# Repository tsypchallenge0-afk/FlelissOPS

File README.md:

# AviFarm · FlelissOPS — Smart Poultry Management System

AviFarm (dashboard brand: **FlelissOPS**) is an IoT + AI platform for commercial poultry houses. ESP32 sensor nodes stream temperature, humidity and ammonia over MQTT; a FastAPI backend stores them in MongoDB, forecasts and detects anomalies, and runs a closed control loop over fans, heaters, lighting and feeders. A multi-tenant React dashboard serves each client on its own sub-domain, with a separate super-admin console.

---

## Architecture

```text
 ESP32 + DHT22 + MQ-135 ──MQTT──►  Mosquitto  ──►┐
 Simulators (HTTP) ─────────────────────────────►├── FastAPI backend (:9000)        React dashboard (:5173)
                                                 │   telemetry · alerts · AI ──WS──► <tenant>.lvh.me
                                                 │   control loop · flocks           super.lvh.me (super admin)
 Actuator ESP32 (fans/heater/…) ◄──MQTT commands─┘          │
                                                        MongoDB
```

| Layer | Tech | Code |
|---|---|---|
| Hardware | ESP32, DHT22, MQ-135, actuator node | [`hardware/`](hardware/) |
| Messaging | MQTT (Mosquitto), WebSockets | [`mosquitto/`](mosquitto/), [`back_end/app/core/mqtt.py`](back_end/app/core/mqtt.py) |
| Backend | FastAPI, PyMongo, APScheduler | [`back_end/app/`](back_end/app/) |
| AI | Prophet forecasting, Isolation-Forest anomalies, rule/AI control loop | [`back_end/app/ai/`](back_end/app/ai/) |
| Frontend | React 19, Vite, Recharts, dnd-kit | [`poultry-dashboard/`](poultry-dashboard/) |

## Features

- **Command Center & House Control** — live gauges (temperature, humidity, ammonia, heat-stress index THI), alerts, manual/AI control of fans, heater, lighting and feeder.
- **Spatial view** — cut-away 3-D house with every sensor at its installed position, an interpolated floor heat-map (temperature / humidity / NH₃), live equipment state, and drag-to-reposition sensors.
- **Flock management** — placements, weigh-ins, feed, mortality; KPIs: mortality %, FCR, weight vs breed standard (Ross 308 / Cobb 500), EPEF; age-based setpoint curves.
- **Health score** — weighted from temperature vs age target, ammonia and survival.
- **AI** — Prophet forecasts, Isolation-Forest anomaly detection, autonomous control loop with a decision log (AI automation rate is measured, not assumed).
- **Analytics & reports** — farm comparison, efficiency, alert patterns, PDF reports and scheduled e-mail reports.
- **Multi-tenancy** — each client on `<subdomain>.lvh.me`, plan quotas, invitations, super-admin console.

---

## Quick start (local)

**Prerequisites:** Docker Desktop, Python 3.11+ (verified on 3.14), Node.js 18+ (verified on 24).

### 1. Infrastructure (MongoDB, Mongo Express, Mosquitto)
```bash
docker compose up -d
```
MongoDB `:27017` (user `admin` / `password`), Mongo Express http://localhost:8081, MQTT `:1883`.

### 2. Backend
```bash
cd back_end
python -m venv .venv
.venv\Scripts\activate            # macOS/Linux: source .venv/bin/activate
pip install -r requirements.txt   # includes PyTorch — large download
copy .env.example .env            # macOS/Linux: cp .env.example .env
uvicorn app.main:app --reload --port 9000
```
API docs: http://localhost:9000/docs. The port must be **9000** — the frontend proxies `/api` there.

### 3. Seed data
```bash
cd back_end
python -m scripts.seed_dev --demo
```
Creates the `default` tenant, alert rules, a **super admin** (`superadmin`) and a **tenant admin** (`admin@test.com`) — the generated passwords are printed once (or set `SEED_SUPERADMIN_PASSWORD` / `SEED_ADMIN_PASSWORD` first). `--demo` adds the simulator's farms/houses/sensors and an active flock with realistic history in every house. Safe to re-run; existing users are left untouched (`--reset-passwords` to change that).

### 4. Frontend
```bash
cd poultry-dashboard
copy .env.example .env
npm install
npm run dev
```

### 5. Open it
| URL | What |
|---|---|
| http://default.lvh.me:5173 | Tenant dashboard (`admin@test.com`) |
| http://super.lvh.me:5173 | Super-admin console (`superadmin`) |
| http://localhost:9000/docs | API |

> The tenant comes from the sub-domain, so use `*.lvh.me`, not `localhost`. `lvh.me` resolves to 127.0.0.1 through **public DNS** — for an offline demo add these lines to `C:\Windows\System32\drivers\etc\hosts` (or `/etc/hosts`):
> ```
> 127.0.0.1  lvh.me default.lvh.me super.lvh.me
> ```
> plus one line per extra tenant sub-domain. Fonts are bundled, so the UI looks identical offline.

### 6. Live data without hardware
```bash
cd back_end
python -m simulator.runner --live      # one reading per simulated sensor per minute
python -m simulator.runner --backfill  # 21 days of history (for AI training/analytics)
```

### 7. Heat-stress demo (about 1 minute)
Open a house → **▶ HEAT-STRESS DEMO** (supervisor/admin). The backend replays a heat wave on that house's real sensors; everything else is the production pipeline: readings are stored and broadcast, alert rules fire (one alert per condition, no flood), the AI decision function runs on the stored data and its commands go out exactly like the 30-second control loop (actuator state, audit log, WebSocket, MQTT to the hardware). The panel shows the phases, peak temperature, alerts and the **measured breach → AI-command latency**. If the fans are in MANUAL mode the AI is, correctly, not allowed to override them. Demo readings are tagged `source: "demo_scenario"`. API: `POST /houses/{id}/demo/heat-stress`, `GET /houses/{id}/demo/status`.

---

## Tests

```bash
cd back_end
pip install -r requirements-dev.txt
set MONGO_URL=mongodb://admin:password@127.0.0.1:27017/?authSource=admin   # export on macOS/Linux
python -m pytest
```
The suite ([`back_end/tests/`](back_end/tests/)) runs against a throw-away `poultry_test` database (created and dropped automatically — it refuses to run against any database not ending in `_test`) and covers auth & tenant isolation, farm → house → device → telemetry → alert flow, flock KPIs, controls, maintenance and super-admin access.

Frontend: `cd poultry-dashboard && npm run lint && npm run build`.

---

## Hardware (MQTT)

**Sensor node** — [`hardware/sensor_node_esp32/`](hardware/sensor_node_esp32/)
- DHT22 (temperature/humidity) on GPIO 4, MQ-135 (ammonia) on GPIO 34.
- Libraries: `DHT sensor library`, `PubSubClient`, `ArduinoJson`.
- Set `ssid`, `password` and `mqtt_server` (the PC's LAN IP) in the `.ino`.

Publish JSON to topic `telemetry/send`:
```json
{ "device_id": "69aac9a67dee4c1c93b052ee", "temperature": 28.5, "humidity": 65.0, "ammonia": 12.4 }
```
The backend looks the device up, tags the reading with its tenant and house, marks it online and evaluates alert rules. Unknown device IDs are listed as discovered devices and can be adopted in the device registration drawer. A sensor that has not reported for 15 minutes is shown offline.

**Actuator node** — [`hardware/actuator_node_esp32/`](hardware/actuator_node_esp32/) receives control commands over MQTT.

**PCBs (revision 2.0, KiCad 9)** — schematics, board layouts, 3D renders and ready-to-order Gerbers for both nodes are in [`hardware/pcb/`](hardware/pcb/); see [`hardware/README.md`](hardware/README.md) for the parts list and notes.

---

## Troubleshooting

| Symptom | Fix |
|---|---|
| Backend: `Authentication failed` from MongoDB on Windows | A local **MongoDB Windows service** also listens on `127.0.0.1:27017` and wins over Docker. Use `MONGO_URL=mongodb://admin:password@[::1]:27017/?authSource=admin` (the default in `.env.example`), or stop the service (`net stop MongoDB`). |
| `Tenant "default" not found` | Open the app on `default.lvh.me`, and run the seed script. |
| Page does not load when offline | Add the hosts-file entries above. |
| `pip install` fails on numpy/pandas | Use the pinned `requirements.txt` (old pins do not support Python 3.13+). |
| Warning `JWT_SECRET is not set` | Set `JWT_SECRET` in `back_end/.env`. |

---

## Project structure

```text
back_end/
  app/            FastAPI routers (auth, farms, houses, devices, telemetry, alerts, flock, ai, control, analytics, reports, tenants)
  simulator/      physics-based sensor simulator
  scripts/        seed_dev.py and maintenance scripts
  tests/          pytest API suite
poultry-dashboard/
  src/pages       Command Center, House Control, Flock, Analytics, Devices, Alerts, Maintenance, Admin, super-admin
  src/components  gauges, spatial FloorPlanView, health dashboard, curve editor …
  src/lib         API client, tenant helpers, shared constants
hardware/         ESP32 firmware (sensor & actuator nodes)
mosquitto/        broker config
```

## License
Proprietary. All rights reserved.

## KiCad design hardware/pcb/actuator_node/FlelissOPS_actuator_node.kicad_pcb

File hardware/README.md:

# Hardware

Two ESP32-WROOM-32 nodes: a **sensor node** that measures the house climate and an **actuator node** that switches equipment. Both talk to the backend over MQTT (topic `telemetry/send` for readings, `commands/{house_id}/{device}` for control).

```
hardware/
├── sensor_node_esp32/      Arduino firmware — sensor node
├── actuator_node_esp32/    Arduino firmware — actuator node
├── i2c_scanner/            utility sketch to find I²C addresses (OLED)
└── pcb/                    PCB design files, revision 2.0 (KiCad 9)
    ├── sensor_node/
    └── actuator_node/
```

Each board folder under `pcb/` contains:

| Path | What it is |
|---|---|
| `*.kicad_pro`, `*.kicad_sch`, `*.kicad_pcb` | KiCad 9 project, schematic and board layout (open the `.kicad_pro`) |
| `exports/*_schematic.pdf` | Schematic, readable without KiCad |
| `exports/*_pcb_layout.pdf` | Copper, silkscreen and outline layers |
| `exports/*_3d_top.png`, `*_3d_bottom.png` | 3D renders of the assembled board |
| `gerbers/` | Gerber and drill files (RS-274X / Excellon) |
| `*_gerbers_*.zip` | The same Gerbers zipped, ready to upload to a PCB fab |

## Sensor node — 100 × 60 mm

| Ref | Part | Role |
|---|---|---|
| U1 | ESP32-WROOM-32 (DevKit header) | Wi-Fi + MQTT |
| U2 | DHT22 | Temperature / humidity, GPIO 4, 10 kΩ pull-up (R1) |
| J2 | MQ-135 module | Air quality / ammonia, analog on GPIO 34 |
| J1 | SSD1306 OLED (I²C) | Local display |
| J3, C1 | Power input + bulk capacitor | |

## Actuator node — 140 × 100 mm

Mains-powered: it draws its own 5 V from the AC line and switches a fan.

| Ref | Part | Role |
|---|---|---|
| U1 | ESP32-WROOM-32 (DevKit header) | Wi-Fi + MQTT |
| PS1 | HLK-PM01 | 230 V AC → 5 V DC |
| U2 | AMS1117-3.3 | 3.3 V regulator |
| K2 | Omron G5LE-1 relay | Switches the fan (J2 *FAN OUTPUT*) |
| Q2, R1, D1 | NPN driver, 10 kΩ base resistor, 1N4007 flyback diode | Relay coil drive |
| F1 | Fuse | On the AC input (J1 *AC INPUT*) |
| WIFI1, MQTT1, ALARM1 + R2–R4 | Status LEDs, 220 Ω | Wi-Fi, broker and alarm state |
| — | SSD1306 OLED (I²C) | Local display |

> **Mains voltage.** The actuator board carries 230 V AC on J1, PS1, F1, K2 and J2. Keep the high-voltage area enclosed and never work on the board while it is plugged in.

## Firmware and PCB revisions

The firmware in `actuator_node_esp32/` was written on the breadboard prototype and drives four outputs (fan PWM on GPIO 18, heater, feeder and lighting relays on GPIO 19, 5 and 23). PCB revision 2.0 carries **one** relay channel (the fan) plus status LEDs and an OLED. Check the pin mapping in the sketch against `exports/actuator_node_schematic.pdf` before flashing the firmware onto the v2.0 board.

## Before flashing

Both sketches ship with placeholders. Set them first:

```cpp
const char* ssid        = "YOUR_WIFI_SSID";
const char* password    = "YOUR_WIFI_PASSWORD";
const char* mqtt_server = "192.168.1.100";   // LAN IP of the PC running Mosquitto
```

Libraries: `PubSubClient`, `ArduinoJson`, `DHT sensor library` (sensor node), `Adafruit SSD1306` + `Adafruit GFX` (OLED).

## Ordering the boards

Upload the `*_gerbers_*.zip` of a board to any PCB fab (2 layers, 1.6 mm FR-4). To regenerate the exports after editing the design:

```bash
kicad-cli sch export pdf -o exports/<board>_schematic.pdf <project>.kicad_sch
kicad-cli pcb render --side top -o exports/<board>_3d_top.png <project>.kicad_pcb
```

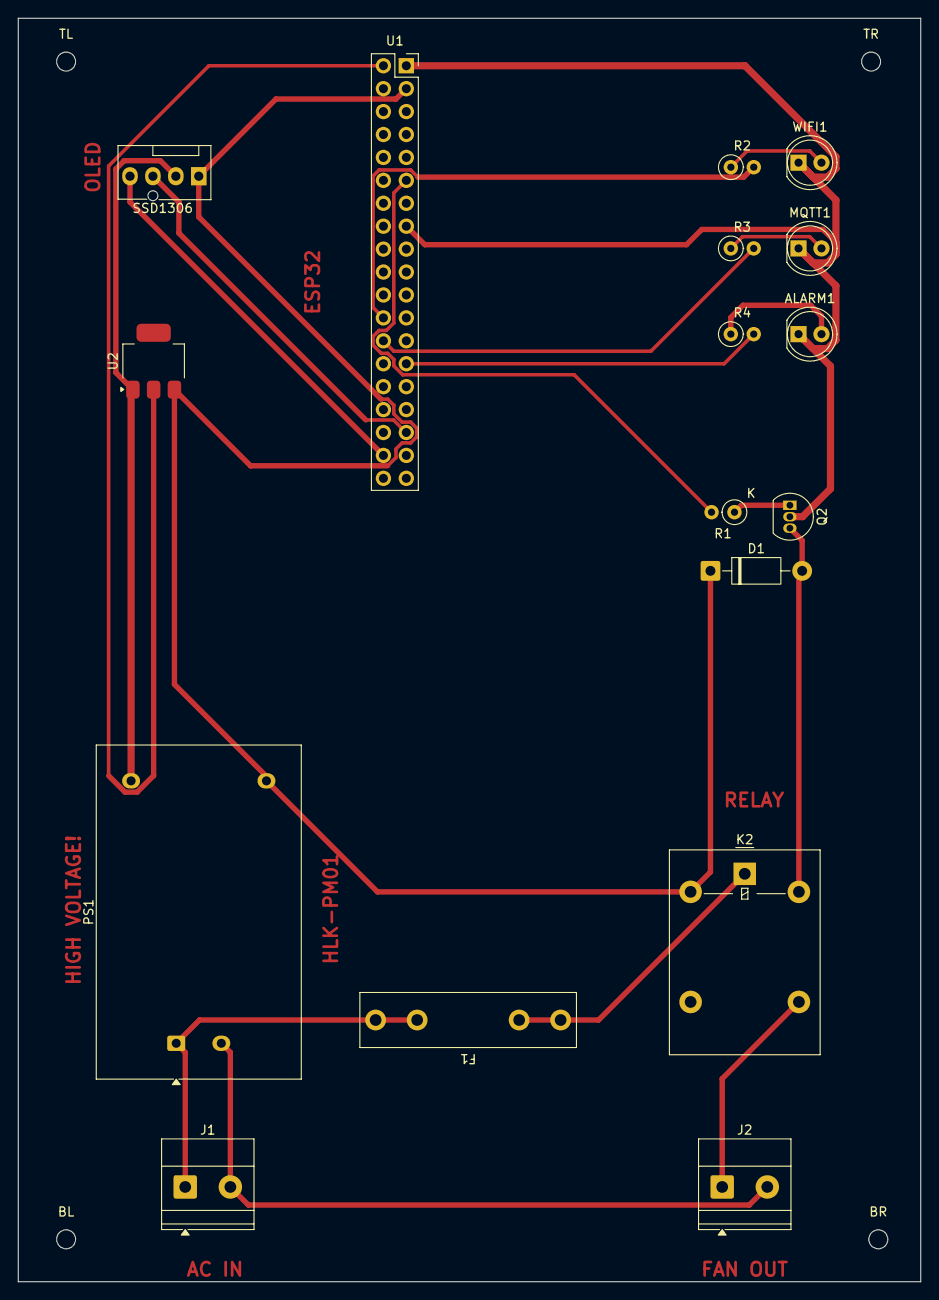
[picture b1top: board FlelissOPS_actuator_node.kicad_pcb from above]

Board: 2 copper layers, 100.0 x 140.0 mm, 21 parts (0 on the bottom side), 18 nets.

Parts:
ALARM1: LED; LED_D5.0mm
BL: MountingHole_2.1mm
BR: MountingHole_2.1mm
D1: 1N4007; D_DO-41_SOD81_P10.16mm_Horizontal
F1: Fuse; Fuseholder_Littelfuse_100_series_5x20mm
J1: AC INPUT; TerminalBlock_Phoenix_MKDS-1,5-2_1x02_P5.00mm_Horizontal
J2: FAN OUTPUT; TerminalBlock_Phoenix_MKDS-1,5-2_1x02_P5.00mm_Horizontal
K2: G5LE-1; Relay_SPDT_Omron-G5LE-1
MQTT1: LED; LED_D5.0mm
PS1: HLK-PM01; Converter_ACDC_Hi-Link_HLK-PMxx
Q2: Q_NPN_BEC; TO-92_Inline
R1: 10 KOhm; R_Axial_DIN0207_L6.3mm_D2.5mm_P2.54mm_Vertical
R2, R3, R4: 220 Ohm; R_Axial_DIN0207_L6.3mm_D2.5mm_P2.54mm_Vertical
SSD1306: OLED Screen; FanPinHeader_1x04_P2.54mm_Vertical
TL: MountingHole_2.1mm
TR: MountingHole_2.1mm
U1: ESP32-WROOM-32; PinSocket_2x19_P2.54mm_Vertical
U2: AMS1117-3.3; SOT-223
WIFI1: LED; LED_D5.0mm

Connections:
+3.3V: U1.2 (VDD), U2.2 (VO)
+5V: D1.1 (K), K2.2, PS1.4 (+Vout), SSD1306.1, U1.3 (EN), U2.3 (VI)
GND: ALARM1.1 (K), MQTT1.1 (K), PS1.3 (-Vout), Q2.2 (E), SSD1306.2, U1.1 (GND), U1.15 (GND), U1.38 (GND), U2.1 (GND), WIFI1.1 (K)
unnamed: ALARM1.2 (A), R4.1
unnamed: D1.2 (A), K2.5, Q2.3 (C)
unnamed: F1.1, K2.1
unnamed: F1.2, J1.1, PS1.1 (AC/L)
unnamed: J1.2, J2.2, PS1.2 (AC/N)
unnamed: J2.1, K2.4
unnamed: MQTT1.2 (A), R3.1
unnamed: Q2.1 (B), R1.1
unnamed: SSD1306.3, U1.33 (IO21)
unnamed: SSD1306.4, U1.36 (IO22)
unnamed: R2.2, U1.24 (IO2)
unnamed: R3.2, U1.26 (IO4)
unnamed: R4.2, U1.27 (IO16)
unnamed: R1.2, U1.11 (IO26)
unnamed: R2.1, WIFI1.2 (A)

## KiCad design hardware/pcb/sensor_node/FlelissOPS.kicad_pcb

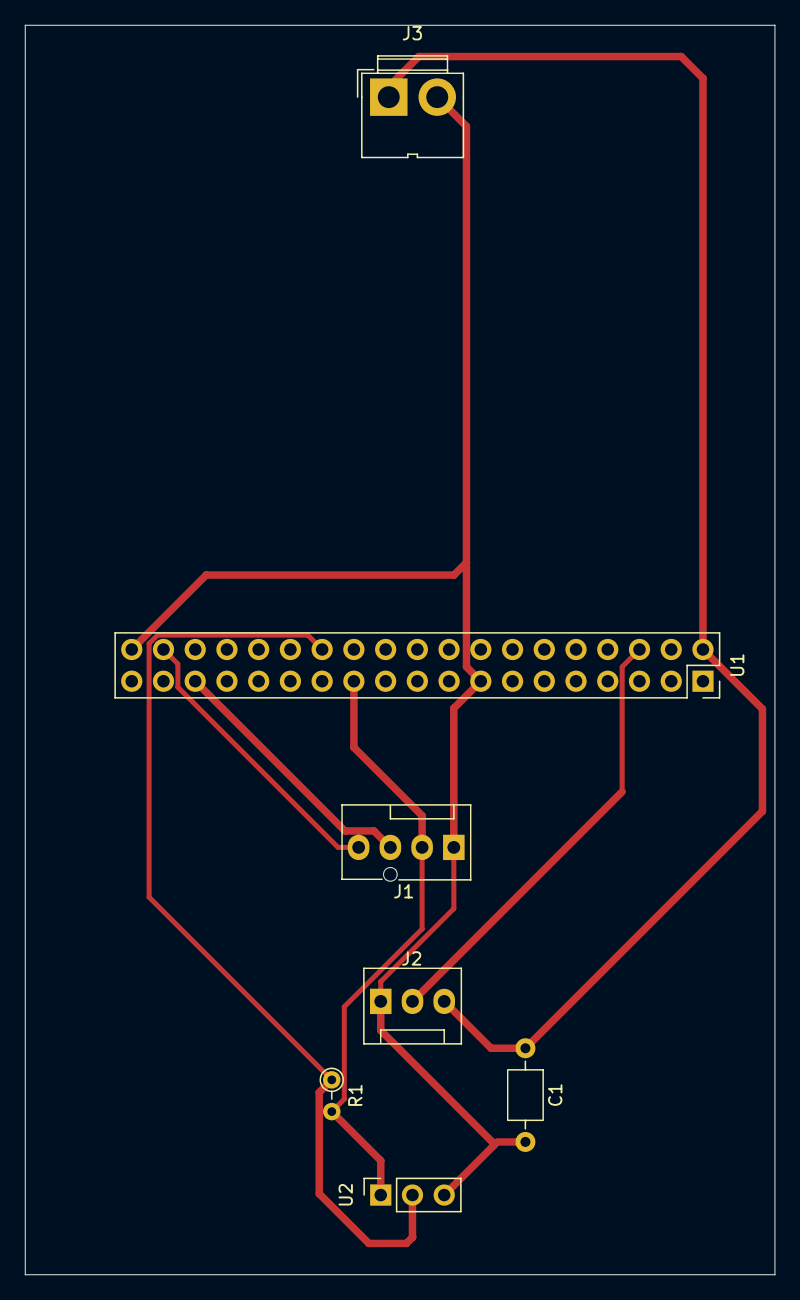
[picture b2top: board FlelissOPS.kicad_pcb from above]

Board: 2 copper layers, 60.0 x 100.0 mm, 7 parts (0 on the bottom side), 7 nets.

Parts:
C1: C; C_Axial_L3.8mm_D2.6mm_P7.50mm_Horizontal
J1: SSD1306; FanPinHeader_1x04_P2.54mm_Vertical
J2: MQ-135; FanPinHeader_1x03_P2.54mm_Vertical
J3: J POWER; JWT_A3963_1x02_P3.96mm_Vertical
R1: 10 KOhm; R_Axial_DIN0204_L3.6mm_D1.6mm_P2.54mm_Vertical
U1: ESP32-WROOM-32; PinSocket_2x19_P2.54mm_Vertical
U2: DHT22; PinSocket_1x03_P2.54mm_Vertical

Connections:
unnamed: C1.2, J1.1 (GND), J2.1, J3.2 (GND), U1.1 (GND), U1.15 (GND), U1.38 (GND), U2.3 (GND)
unnamed: J1.4 (SCL), U1.36 (IO22)
unnamed: J1.3 (SDA), U1.33 (IO21)
unnamed: J1.2 (VCC), R1.2, U1.23 (IO15), U2.1 (VDD)
unnamed: J2.2, U1.6 (IO34)
unnamed: C1.1, J2.3, J3.1 (5V), U1.2 (VDD)
unnamed: R1.1, U1.26 (IO4), U2.2 (SDA)
